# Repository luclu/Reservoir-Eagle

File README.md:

# Reservoir-Eagle

4 Channel self-refilling Liquid Reservoir
updates soon..

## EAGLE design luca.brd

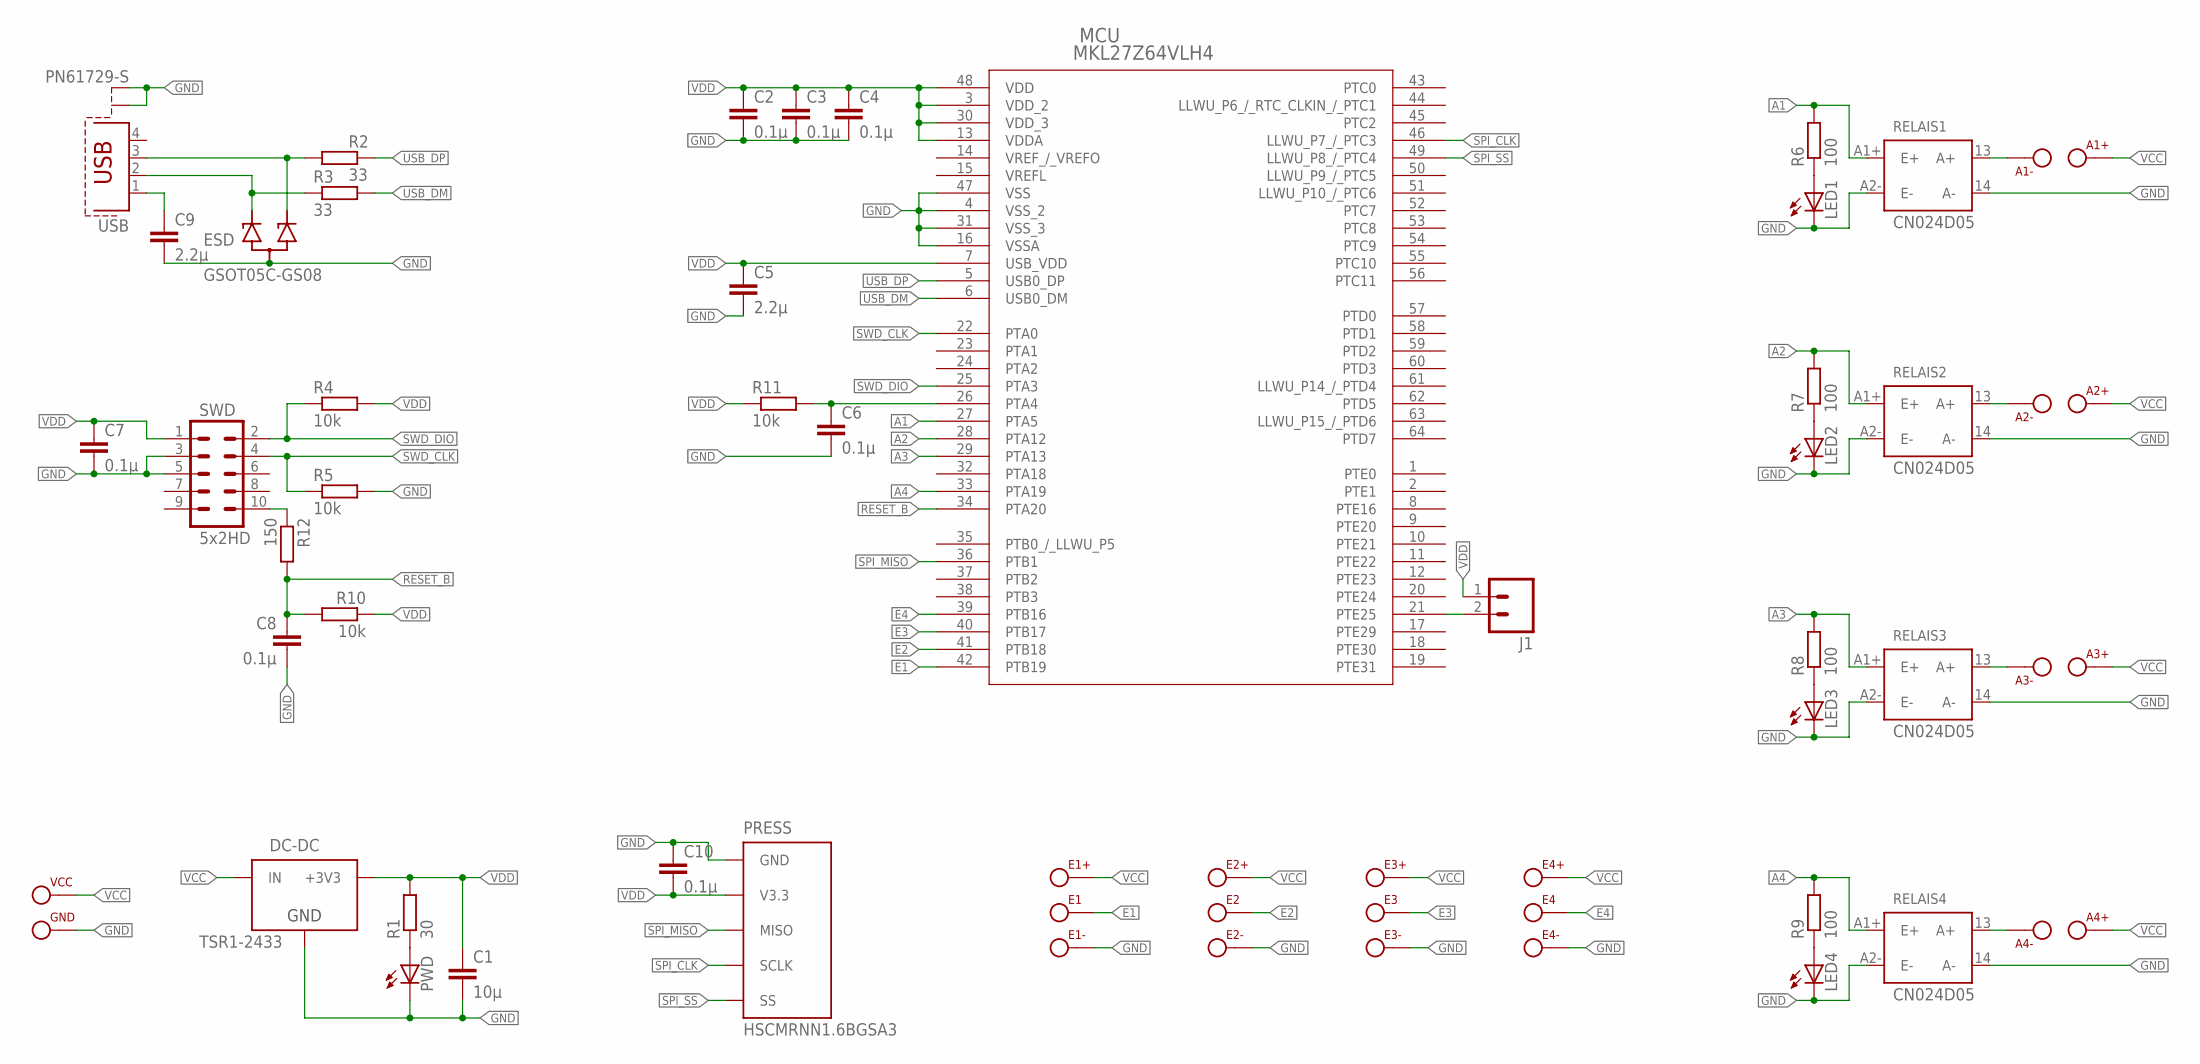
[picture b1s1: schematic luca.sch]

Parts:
A1+, A1-, A2+, A2-, A3+, A3-, A4+, A4-: FFKDS-2,54; FFSDK-2,54
C1: 10µ; C1206
C2, C3, C4, C6, C7, C8, C10: 0.1µ; C1206
C5, C9: 2.2µ; C1206
DC-DC: TSR1-2433; TSR-1
E1, E1+, E1-, E2, E2+, E2-, E3, E3+, E3-, E4, E4+, E4-: FFKDS-2,54; FFSDK-2,54
ESD: GSOT05C-GS08
GND: FFKDS-2,54; FFSDK-2,54
J1: M02LOCK; 1X02_LOCK
LED1, LED2, LED3, LED4: LED
MCU: MKL27Z64VLH4; 98ASS23234W
PRESS: HSCMRNN1.6BGSA3
PWD: LED
R1: 30; M1206
R2, R3: 33; M1206
R4, R5, R10, R11: 10k; M1206
R6, R7, R8, R9: 100; M1206
R12: 150; M1206
RELAIS1, RELAIS2, RELAIS3, RELAIS4: CN024D05
SWD: 5x2HD; 2X5-PTH-1.27MM
USB: PN61729-S
VCC: FFKDS-2,54; FFSDK-2,54

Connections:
A1: MCU.27 (PTA5), R6.2, RELAIS1.A1+ (E+)
A2: MCU.28 (PTA12), R7.2, RELAIS2.A1+ (E+)
A3: MCU.29 (PTA13), R8.2, RELAIS3.A1+ (E+)
A4: MCU.33 (PTA19), R9.2, RELAIS4.A1+ (E+)
E1: E1.1, E1.2, MCU.42 (PTB19)
E2: E2.1, E2.2, MCU.41 (PTB18)
E3: E3.1, E3.2, MCU.40 (PTB17)
E4: E4.1, E4.2, MCU.39 (PTB16)
GND: C1.2, C2.2, C3.2, C4.2, C5.2, C6.2, C7.2, C8.2, C9.2, C10.1, DC-DC.2 (GND), E1-.1, E1-.2, E2-.1, E2-.2, E3-.1, E3-.2, E4-.1, E4-.2, ESD.P$3, GND.1, GND.2, LED1.B (C), LED2.B (C), LED3.B (C), LED4.B (C), MCU.4 (VSS_2), MCU.16 (VSSA), MCU.31 (VSS_3), MCU.47 (VSS), PRESS.P$1 (GND), PWD.B (C), R5.2, RELAIS1.14 (A-), RELAIS1.A2- (E-), RELAIS2.14 (A-), RELAIS2.A2- (E-), RELAIS3.14 (A-), RELAIS3.A2- (E-), RELAIS4.14 (A-), RELAIS4.A2- (E-), SWD.3, SWD.5, USB.S1, USB.S2
unnamed: ESD.P$1, R2.1, USB.3
unnamed: ESD.P$2, R3.1, USB.2
unnamed: C9.1, USB.1
unnamed: LED2.A, R7.1
unnamed: LED1.A, R6.1
unnamed: A1-.1, A1-.2, RELAIS1.13 (A+)
unnamed: LED3.A, R8.1
unnamed: PWD.A, R1.1
unnamed: A3-.1, A3-.2, RELAIS3.13 (A+)
unnamed: LED4.A, R9.1
unnamed: A4-.1, A4-.2, RELAIS4.13 (A+)
unnamed: J1.2, MCU.21 (PTE25)
unnamed: A2-.1, A2-.2, RELAIS2.13 (A+)
unnamed: R12.1, SWD.10
NMI_B: C6.1, MCU.26 (PTA4), R11.2
RESET_B: C8.1, MCU.34 (PTA20), R10.2, R12.2
SPI_CLK: MCU.46 (LLWU_P7_/_PTC3), PRESS.P$4 (SCLK)
SPI_MISO: MCU.36 (PTB1), PRESS.P$3 (MISO)
SPI_SS: MCU.49 (LLWU_P8_/_PTC4), PRESS.P$5 (SS)
SWD_CLK: MCU.22 (PTA0), R5.1, SWD.4
SWD_DIO: MCU.25 (PTA3), R4.1, SWD.2
USB_DM: MCU.6 (USB0_DM), R3.2
USB_DP: MCU.5 (USB0_DP), R2.2
VCC: A1+.1, A1+.2, A2+.1, A2+.2, A3+.1, A3+.2, A4+.1, A4+.2, DC-DC.1 (IN), E1+.1, E1+.2, E2+.1, E2+.2, E3+.1, E3+.2, E4+.1, E4+.2, VCC.1, VCC.2
VDD: C1.1, C2.1, C3.1, C4.1, C5.1, C7.1, C10.2, DC-DC.3 (+3V3), J1.1, MCU.3 (VDD_2), MCU.7 (USB_VDD), MCU.13 (VDDA), MCU.30 (VDD_3), MCU.48 (VDD), PRESS.P$2 (V3.3), R1.2, R4.2, R10.1, R11.1, SWD.1
VREFL: MCU.15 (VREFL)
VREF_/_VREFO: MCU.14 (VREF_/_VREFO)

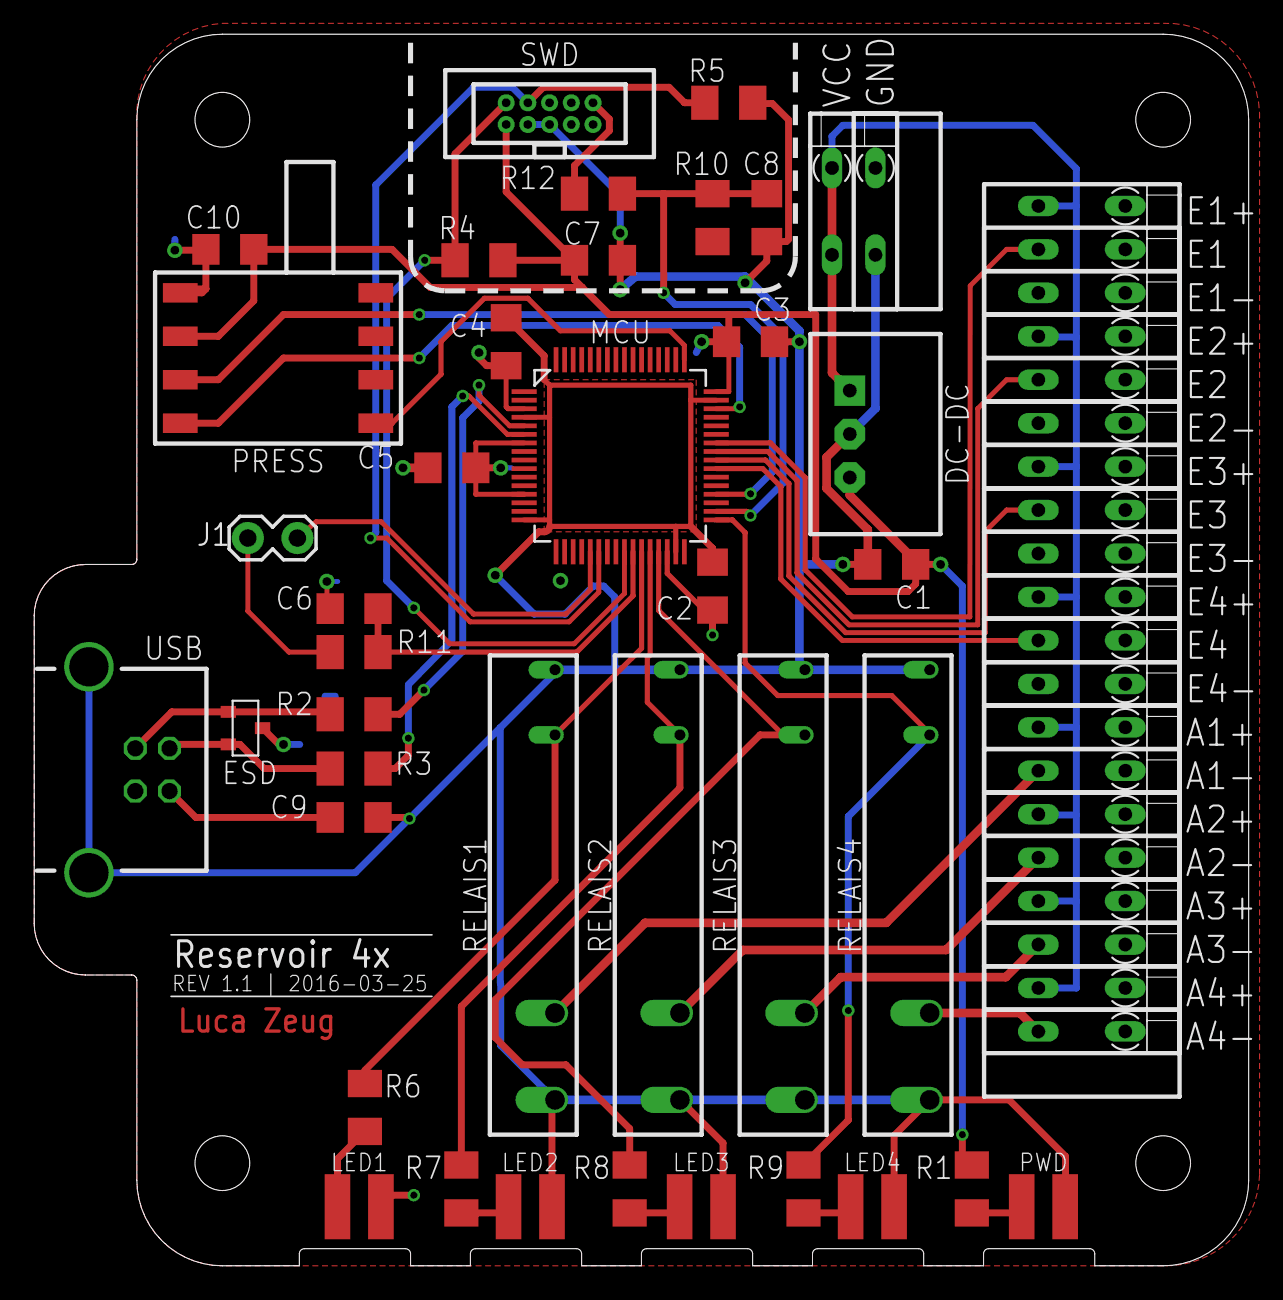
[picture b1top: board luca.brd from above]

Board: 2 copper layers, 71.0 x 72.0 mm, 60 parts (0 on the bottom side), 34 nets.

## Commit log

2016-03-15 Auftragsfertigung Rev 1.0
2016-03-15 ESD, added Pull-Rs, refactored Dimensions
2016-03-16 removed unnecessary caps, green LEDs R -> 100
2016-03-17 added libs
2016-03-18 added config jumper
2016-03-18 fixed board curves
2016-03-25 Refactoring ESD, NMI
2016-03-25 clean-ups
2016-03-27 fixed Jumper
2016-04-23 pcb pic

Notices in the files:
parts and their libraries:
SparkFun-Connectors: Licensing: Creative Commons ShareAlike 4.0 International - https://creativecommons.org/licenses/by-sa/4.0
